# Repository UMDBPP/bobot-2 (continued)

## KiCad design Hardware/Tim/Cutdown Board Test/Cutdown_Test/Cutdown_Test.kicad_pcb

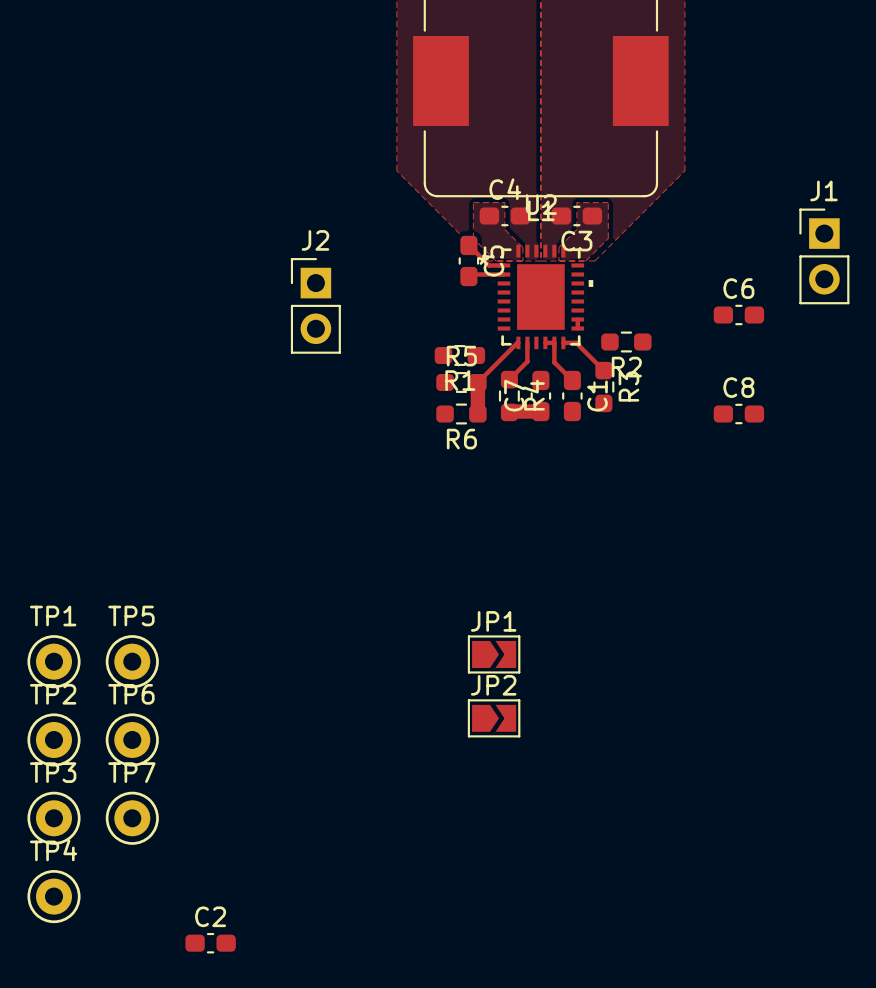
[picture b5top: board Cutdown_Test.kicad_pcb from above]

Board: 2 copper layers, 27 parts (0 on the bottom side), 18 nets.

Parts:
C1: 4.7uF; C_0603_1608Metric_Pad1.08x0.95mm_HandSolder
C2: 10uF; C_0603_1608Metric_Pad1.08x0.95mm_HandSolder
C3, C4: 220nF; C_0603_1608Metric_Pad1.08x0.95mm_HandSolder
C5: 22nF; C_0603_1608Metric_Pad1.08x0.95mm_HandSolder
C6, C8: 22uF; C_0603_1608Metric_Pad1.08x0.95mm_HandSolder
C7: 680p; C_0603_1608Metric_Pad1.08x0.95mm_HandSolder
J1: Nichrome; PinHeader_1x02_P2.54mm_Vertical
J2: Power Input; PinHeader_1x02_P2.54mm_Vertical
JP1, JP2: SolderJumper_2_Open; SolderJumper-2_P1.3mm_Open_TrianglePad1.0x1.5mm
L1: 3.3uH; L_Bourns_SRP1265A
R1: 81.1k; R_0603_1608Metric_Pad0.98x0.95mm_HandSolder
R2: 5m; R_0603_1608Metric_Pad0.98x0.95mm_HandSolder
R3: 75k; R_0603_1608Metric_Pad0.98x0.95mm_HandSolder
R4: 56.2k; R_0603_1608Metric_Pad0.98x0.95mm_HandSolder
R5, R6: 154k; R_0603_1608Metric_Pad0.98x0.95mm_HandSolder
TP1, TP2, TP3, TP4, TP5, TP6, TP7: TestPoint; TestPoint_Keystone_5000-5004_Miniature
U2: LT3120JV-PBF; LQFN28_Rev0_ADI-M

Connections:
+3V3: JP1.1 (A), TP2.1
+BATT: J2.1, JP2.1 (A), R2.1, U2.5 (ISP)
GND: C1.2, C2.2, C6.2, C7.2, C8.2, J1.2, J2.2, R1.2, R3.2, R6.2, U2.3 (GND), U2.11 (GND), U2.18 (GND), U2.22 (GND), U2.29 (PGND)
unnamed: C3.2, L1.1, U2.24 (SW1), U2.25 (SW1)
unnamed: C4.2, L1.2, U2.26 (SW2), U2.27 (SW2)
unnamed: C7.1, R4.2
unnamed: C5.2, C6.1, C8.1, J1.1, R5.1, TP6.1, U2.2 (PVOUT), U2.4 (PVOUT)
unnamed: JP1.2 (B), JP2.2 (B), TP7.1, U2.17 (VIN)
unnamed: C3.1, U2.23 (BST1)
unnamed: C4.1, U2.28 (BST2)
unnamed: C5.1, U2.1 (BST3)
unnamed: C2.1, R2.2, TP3.1, U2.6 (ISN), U2.15 (SYNC/MODE), U2.16 (EN/UVLO), U2.19 (PVIN), U2.20 (PVIN), U2.21 (PVIN)
unnamed: R5.2, R6.1, U2.9 (FB)
unnamed: C1.1, TP4.1, U2.12 (MPCC), U2.13 (VCC)
unnamed: TP1.1, U2.7 (PGOOD)
unnamed: R1.1, U2.8 (PROG)
unnamed: R3.1, U2.14 (RT)
unnamed: R4.1, TP5.1, U2.10 (VC)

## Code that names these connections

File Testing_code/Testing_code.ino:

//Libraries
#include<MS5607.h>
#include<Wire.h>

MbedI2C i2c(6,7);

//Objects
MS5607 P_Sens;

//GPIO Declarations
int SPIO_POCI = 0;
int SPIO_CS_RAD = 1;
int SPIO_SCK = 2;
int SPIO_PICO = 3;
int CROSS_PRIMTX_REDRX = 4;
int CROSS_PRIMRX_REDTX = 5;
int SDA = 6;
int SCL = 7;
int D1 = 8;
int SPIO_CS_IMU = 9;
int LS2 = 10;
int PWM_MC = 11;
int GPS_RX = 12;
int GPS_TX = 13;
int LS1 = 14;
int CH_1A = 15;
int CH_1B = 16;
int CH_2A = 17;
int CH_2B = 18;
int CH_3A = 19;
int CH_3B = 20;
int SPIO_CS_SD = 21;
int SW = 22;
int DIO1 = 23;
int BUSY = 24;
int RST = 25;
int TXEN = 26;
int TIME_PULSE = 27;
int STEP = 28;
int DIRT = 29;

//Variables
float P_val,T_val,H_val;

// the setup function runs once when you press reset or power the board
void setup() {
  Serial.begin(9600); //Start Serial comms
  if(!P_Sens.begin()){
    Serial.println("Error in Communicating with sensor, check your connections!");
  }else{
    Serial.println("MS5607 initialization successful!");
  }
}

// the loop function runs over and over again forever
void loop() {
   if(P_Sens.readDigitalValue()){
    T_val = P_Sens.getTemperature();
    P_val = P_Sens.getPressure();
    H_val = P_Sens.getAltitude();
    Serial.print("Temperature :  ");
    Serial.print(T_val);
    Serial.println(" C");
    Serial.print("Pressure    :  ");
    Serial.print(P_val);
    Serial.println(" mBar");
    Serial.print("Altitude    :  ");
    Serial.print(H_val);
    Serial.println(" meter");
  }else{
    Serial.println("Error in reading digital value in sensor!");
  }
  delay(5000);
}

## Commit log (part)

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2023-10-18 init KiCad projects
2023-10-18 copy paste go brrrr
2023-10-25 silliness
2023-10-26 I think I added the IMU mostly
2023-10-26 IMU should be done
2023-10-30 IMU done maybe?
2023-11-01 added tim folder
2023-11-01 modified calcs
2023-11-01 revised distance calcs
2023-11-02 screwed up the cals
2023-11-02 organized a few things
2023-11-02 Added folder for Tim electronic
2023-11-02 Some organization and connectors for external stuffs
2023-11-03 restructuring
2023-11-03 kicad lib submodule
2023-11-04 submodule shenanigans
2023-11-06 winder regulator controller circuit
2023-11-08 motor controller and h-bridge stuff
2023-11-08 more h-bridge shenanigans and 2 phase power (cringe)
2023-11-10 Redundantcy started
2023-11-16 Reduntant board has all the stuff?
2024-01-22 Added color sensors disconnected GPIO in muxing crisis
2024-01-30 Made it all one board due to large space allowed
2024-02-08 routing started
2024-02-09 Routing donish maybe
2024-02-10 Routing actually done and made smaller????
2024-02-15 Adjusted/added things
2024-03-01 Resistor size change
2024-03-05 fixed the drc things that are problems
2024-03-29 minor changes
2024-04-17 Update changes hopefully good
2024-04-17 Updated things
2024-04-26 Double checking everything is pushed
2024-06-19 Pressure temp done if so inclined add 2nd order compensation
2024-07-02 Working motor control encoders
2024-08-02 SD card workied like 3 weeks ago but im pushing now
2024-09-06 Local SDK maybe
2024-09-06 fixing submodules
2024-09-06 More submodule fixes
2024-09-06 please work
2024-09-13 Fixed cmake file and adjusted gitignore
2024-09-13 Fixing git ignore
2024-09-14 new board w/ teensy
2024-09-14 new board w/ teensy and cleanup
2024-09-14 removed libraries
2024-09-14 added libraries
2024-09-14 added source and docs
2024-09-15 restructure for Shippy
2024-09-15 added comments to CMkeLists.txt for extra explanation
2024-09-15 more documentation
2024-09-21 latest changes
2024-10-23 latest board
2024-10-26 finished wiring
2024-10-26 actually done with schematic
2024-10-27 started working on layout
2024-11-04 First draft of final
2024-11-04 minor changes, more needed
2025-01-23 covid push i dizzyy
2025-01-23 drowst covid pushh
2025-01-31 recovered from covid push
2025-04-04 fixing my opsec
2026-02-19 added folder
2026-02-23 added pranav-pk folder
